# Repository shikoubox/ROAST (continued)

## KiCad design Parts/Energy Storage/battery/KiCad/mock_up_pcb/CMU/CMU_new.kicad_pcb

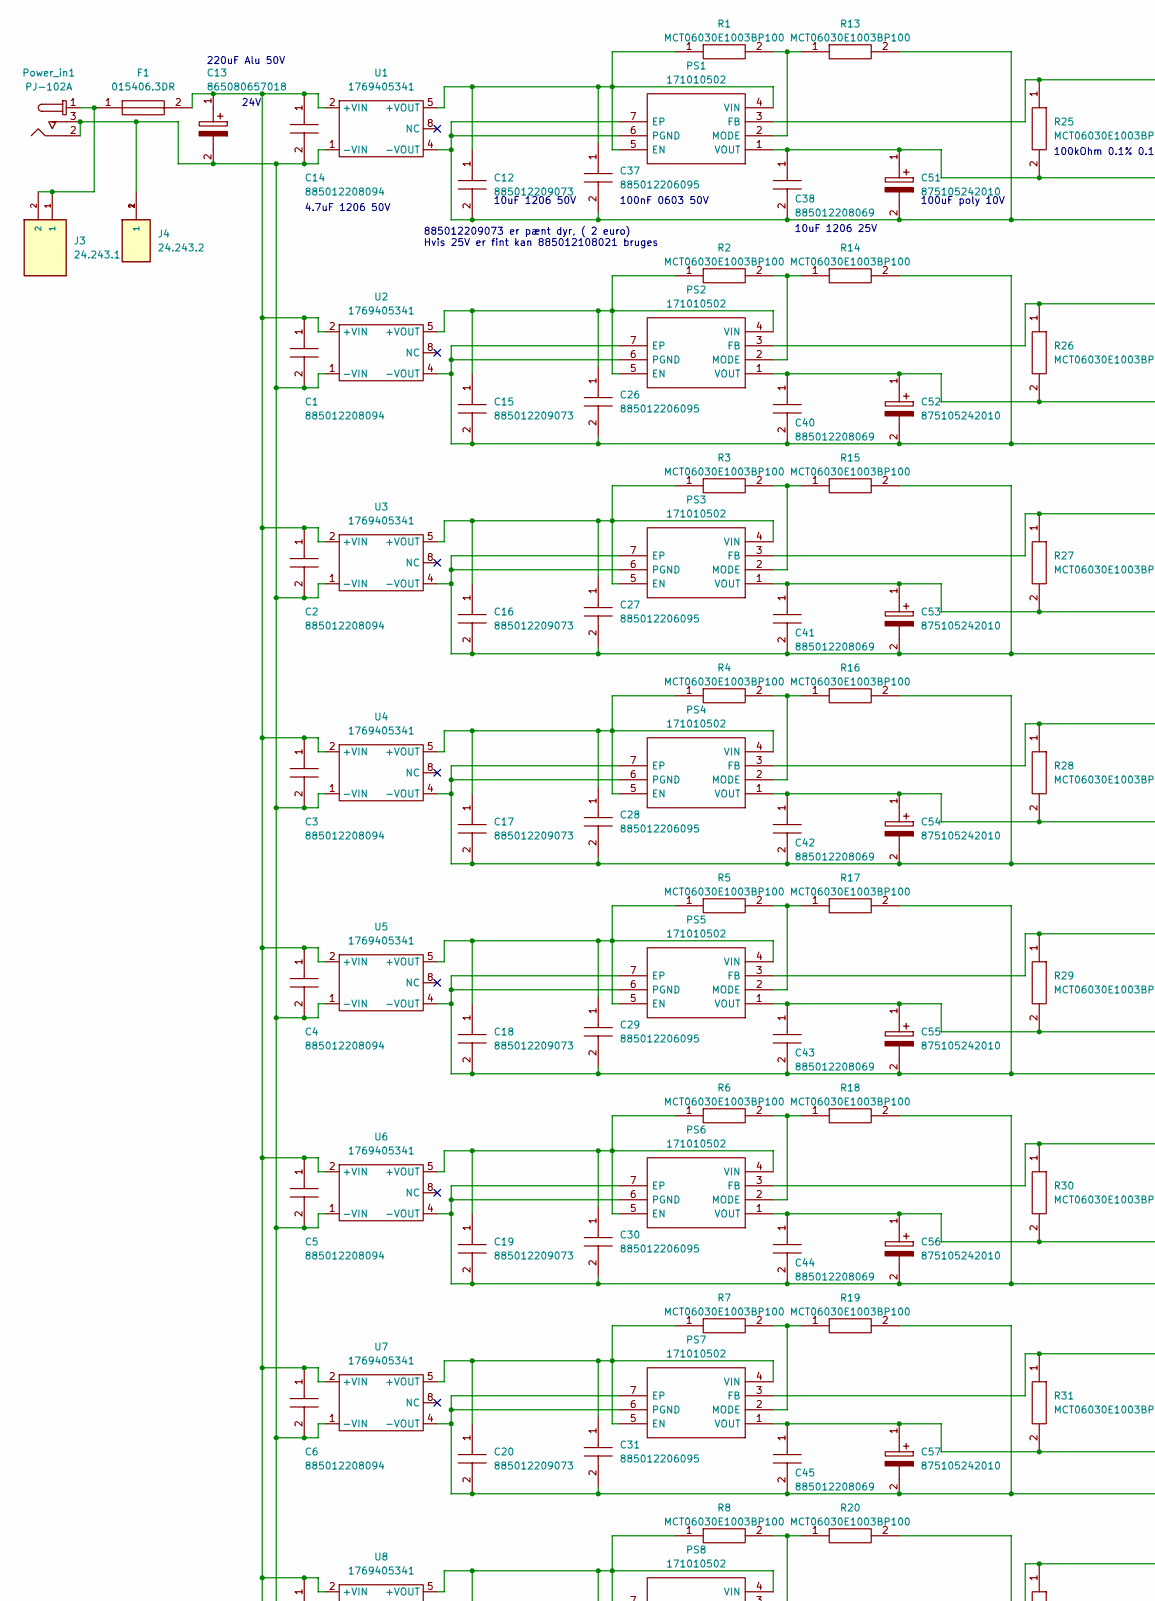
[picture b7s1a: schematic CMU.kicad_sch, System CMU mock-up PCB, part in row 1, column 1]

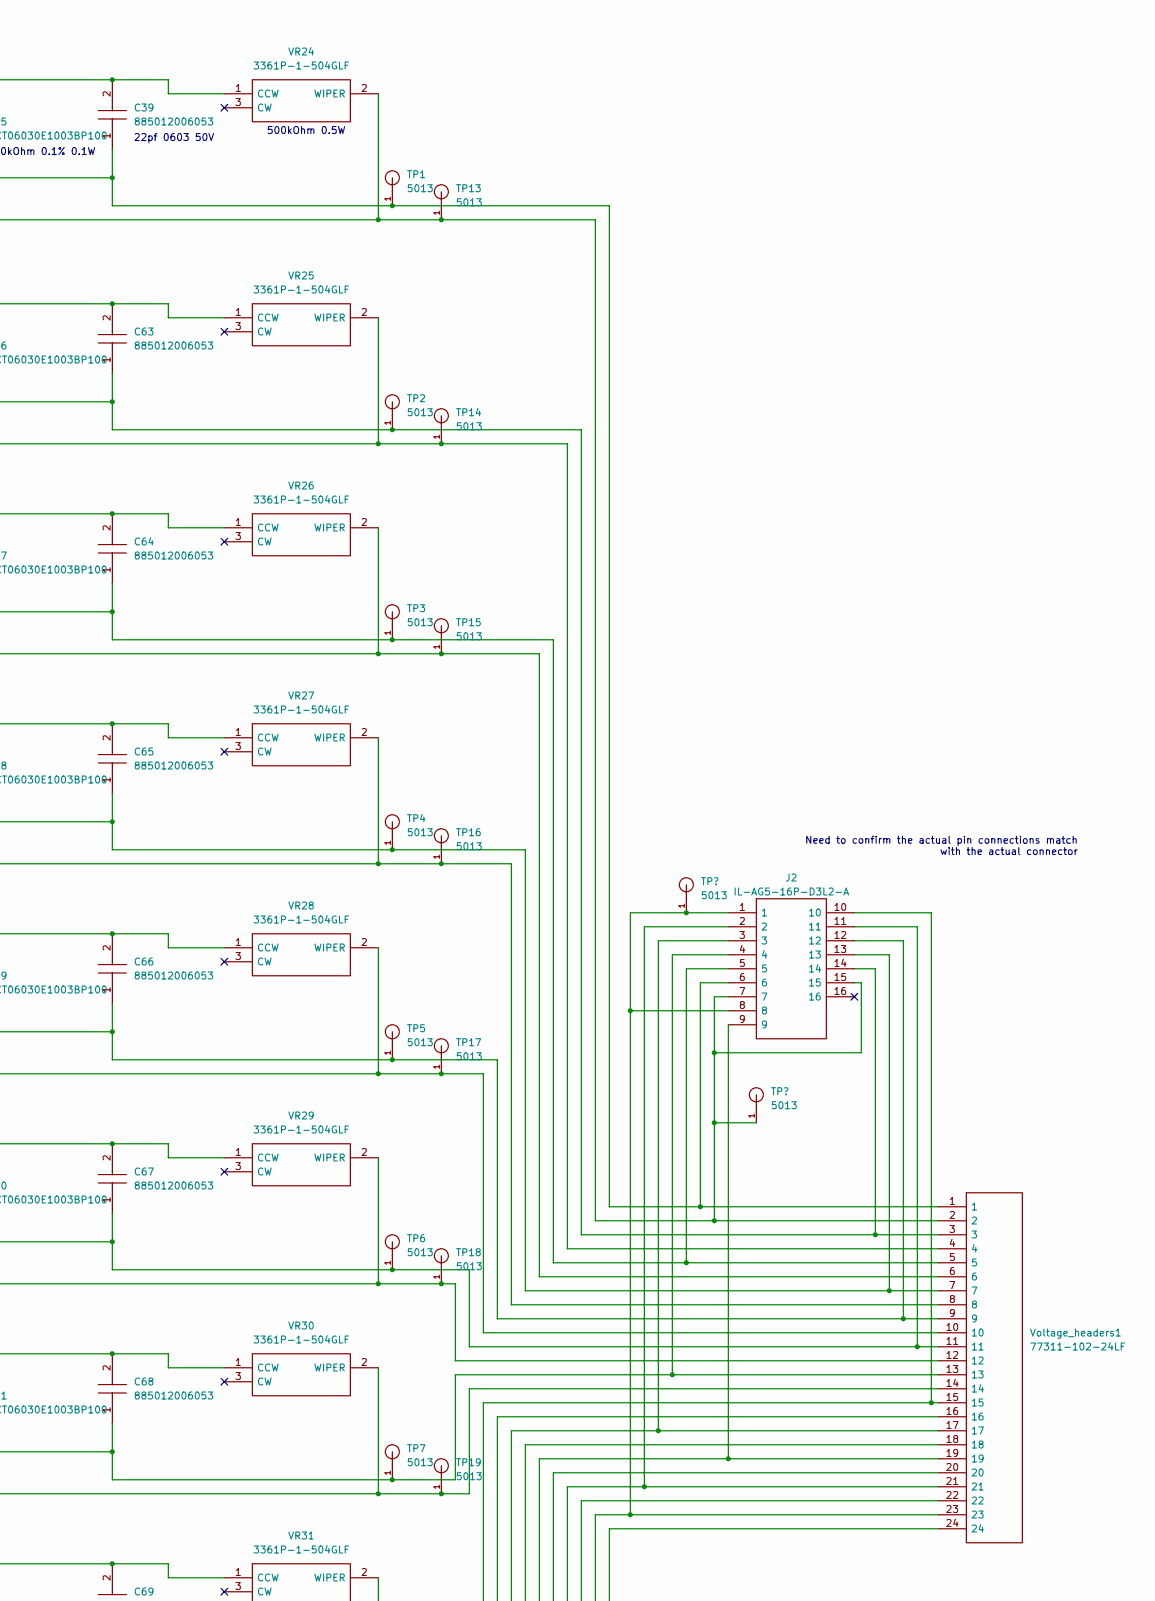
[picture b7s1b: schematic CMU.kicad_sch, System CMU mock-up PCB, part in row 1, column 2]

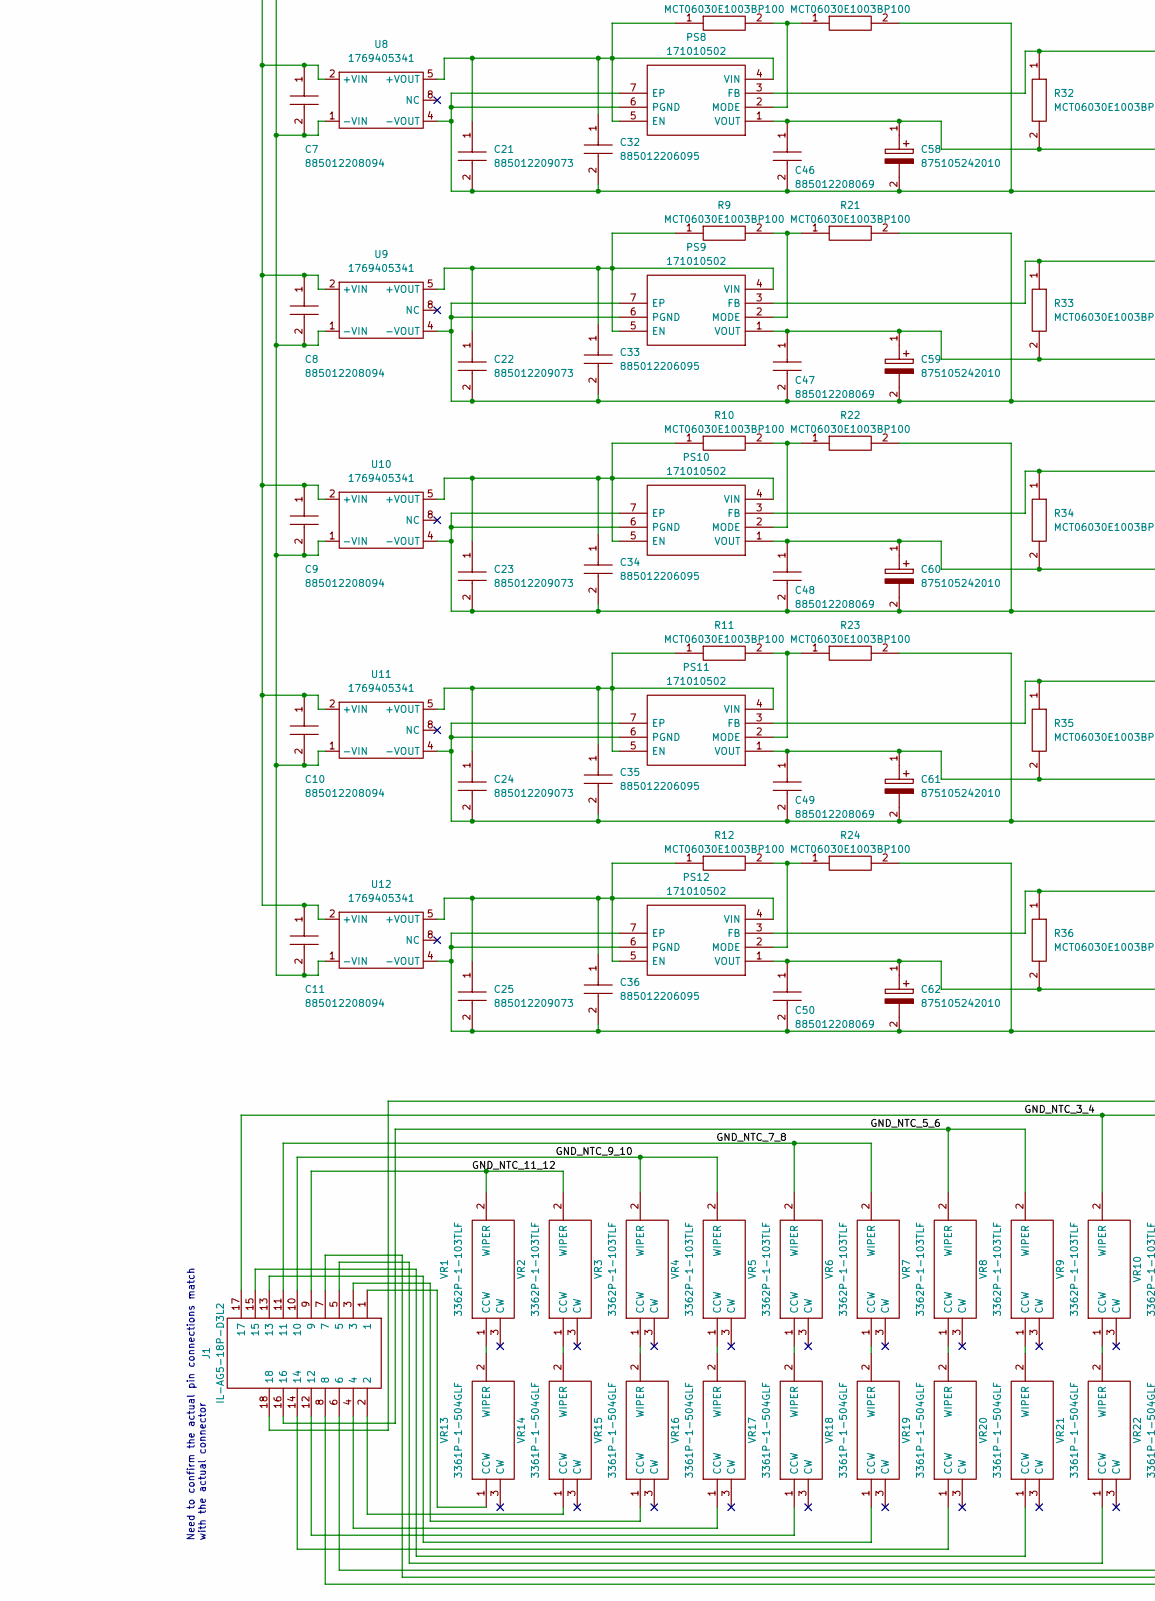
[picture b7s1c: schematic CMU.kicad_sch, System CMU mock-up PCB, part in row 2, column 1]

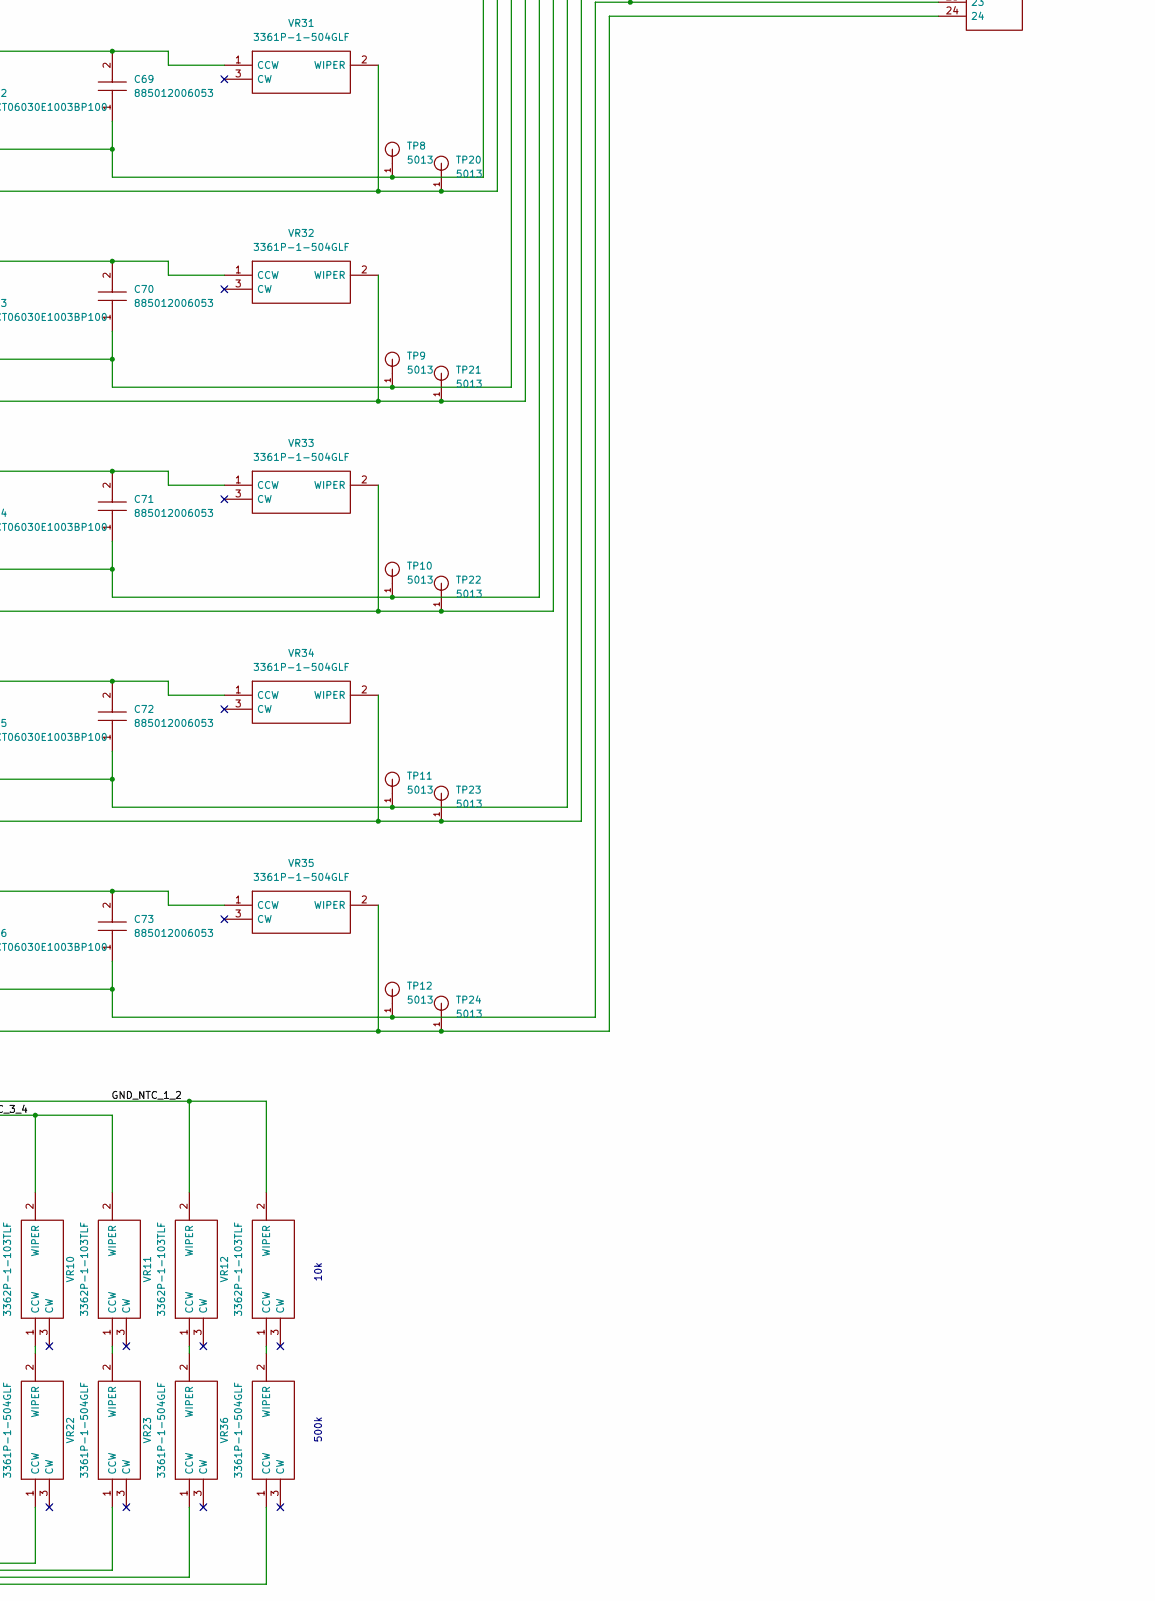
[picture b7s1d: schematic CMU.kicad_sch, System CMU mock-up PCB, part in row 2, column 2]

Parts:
C1, C2, C3, C4, C5, C6, C7, C8, C9, C10, C11, C14: 885012208094; CAPC3216X180N; Mouser Part Number 710-885012208094
C12, C15, C16, C17, C18, C19, C20, C21, C22, C23, C24, C25: 885012209073; CAPC3225X280N; Mouser Part Number 710-885012209073
C13: 865080657018; CAPAE1030X1050N; Mouser Part Number 710-865080657018
C26, C27, C28, C29, C30, C31, C32, C33, C34, C35, C36, C37: 885012206095; CAPC1608X87N; Mouser Part Number 710-885012206095
C38, C40, C41, C42, C43, C44, C45, C46, C47, C48, C49, C50: 885012208069; CAPC3216X180N; Mouser Part Number 710-885012208069
C39, C63, C64, C65, C66, C67, C68, C69, C70, C71, C72, C73: 885012006053; CAPC1608X87N; Mouser Part Number 710-885012006053
C51, C52, C53, C54, C55, C56, C57, C58, C59, C60, C61, C62: 875105242010; CAPAE530X550N; Mouser Part Number 710-875105242010
F1: 015406.3DR; 0154063DR; Mouser Part Number 576-015406.3DR
J1: IL-AG5-18P-D3L2; ILAG518PD3L2; Mouser Part Number 656-IL-AG5-18P-D3L2
J2: IL-AG5-16P-D3L2-A; ILAG516PD3L2A; Mouser Part Number 656-ILAG516PD3L2A
J3: 24.243.1; 242431; Manufacturer_Part_Number 24.243.1
J4: 24.243.2; MULTICOMP_24.243.2; PARTREV 1.0
PS1, PS2, PS3, PS4, PS5, PS6, PS7, PS8, PS9, PS10, PS11, PS12: 171010502; Mouser Part Number 710-171010502
Power_in1: PJ-102A; Barrel_Jack_5.5mmODx2.1mmID_PJ-102A; MPN PJ-102A; Digi-Key_PN CP-102A-ND
R1, R2, R3, R4, R5, R6, R7, R8, R9, R10, R11, R12, R13, R14, R15, R16, R17, R18, R19, R20, R21, R22, R23, R24, R25, R26, R27, R28, R29, R30, R31, R32, R33, R34, R35, R36: MCT06030E1003BP100; RESC1608X55N; Mouser Part Number 594-MCT06030E1003BP1
TP1, TP2, TP3, TP4, TP5, TP6, TP7, TP8, TP9, TP10, TP11, TP12, TP13, TP14, TP15, TP16, TP17, TP18, TP19, TP20, TP21, TP22, TP23, TP24: 5013; TESTPOINT_5013; PARTREV F
U1, U2, U3, U4, U5, U6, U7, U8, U9, U10, U11, U12: 1769405341
VR1, VR2, VR3, VR4, VR5, VR6, VR7, VR8, VR9, VR10, VR11, VR12: 3362P-1-103TLF; 3296P-1-103; Mouser Part Number 652-3362P-1-103TLF
VR13, VR14, VR15, VR16, VR17, VR18, VR19, VR20, VR21, VR22, VR23, VR24, VR25, VR26, VR27, VR28, VR29, VR30, VR31, VR32, VR33, VR34, VR35, VR36: 3361P-1-504GLF; 3361P1253GLF; Mouser Part Number 652-3361P-1-504GLF
Voltage_headers1: 77311-102-24LF; HDRV24W62P0X254_1X24_6096X240X858P; Mouser Part Number 649-77311-102-24LF

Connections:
/GND_NTC_1_2: J1.18, VR11.2 (WIPER), VR12.2 (WIPER)
/GND_NTC_3_4: J1.17, VR9.2 (WIPER), VR10.2 (WIPER)
/GND_NTC_5_6: J1.16, VR7.2 (WIPER), VR8.2 (WIPER)
/GND_NTC_7_8: J1.11, VR5.2 (WIPER), VR6.2 (WIPER)
/GND_NTC_9_10: J1.10, VR3.2 (WIPER), VR4.2 (WIPER)
/GND_NTC_11_12: J1.9, VR1.2 (WIPER), VR2.2 (WIPER)
unnamed: C1.1, C2.1, C3.1, C4.1, C5.1, C6.1, C7.1, C8.1, C9.1, C10.1, C11.1, C13.1, C14.1, F1.2, U1.2 (+VIN), U2.2 (+VIN), U3.2 (+VIN), U4.2 (+VIN), U5.2 (+VIN), U6.2 (+VIN), U7.2 (+VIN), U8.2 (+VIN), U9.2 (+VIN), U10.2 (+VIN), U11.2 (+VIN), U12.2 (+VIN)
unnamed: C1.2, C2.2, C3.2, C4.2, C5.2, C6.2, C7.2, C8.2, C9.2, C10.2, C11.2, C13.2, C14.2, J4.1, J4.2 (1), Power_in1.2, Power_in1.3, U1.1 (-VIN), U2.1 (-VIN), U3.1 (-VIN), U4.1 (-VIN), U5.1 (-VIN), U6.1 (-VIN), U7.1 (-VIN), U8.1 (-VIN), U9.1 (-VIN), U10.1 (-VIN), U11.1 (-VIN), U12.1 (-VIN)
unnamed: C12.1, C37.1, PS1.4 (VIN), PS1.5 (EN), R1.1, U1.5 (+VOUT)
unnamed: C12.2, C37.2, C38.2, C51.2, J2.7, J2.15, PS1.6 (PGND), PS1.7 (EP), R13.2, TP13.1, U1.4 (-VOUT), VR24.2 (WIPER), Voltage_headers1.2
unnamed: C15.1, C26.1, PS2.4 (VIN), PS2.5 (EN), R2.1, U2.5 (+VOUT)
unnamed: C15.2, C26.2, C40.2, C52.2, PS2.6 (PGND), PS2.7 (EP), R14.2, TP14.1, U2.4 (-VOUT), VR25.2 (WIPER), Voltage_headers1.4
unnamed: C16.1, C27.1, PS3.4 (VIN), PS3.5 (EN), R3.1, U3.5 (+VOUT)
unnamed: C16.2, C27.2, C41.2, C53.2, PS3.6 (PGND), PS3.7 (EP), R15.2, TP15.1, U3.4 (-VOUT), VR26.2 (WIPER), Voltage_headers1.6
unnamed: C17.1, C28.1, PS4.4 (VIN), PS4.5 (EN), R4.1, U4.5 (+VOUT)
unnamed: C17.2, C28.2, C42.2, C54.2, PS4.6 (PGND), PS4.7 (EP), R16.2, TP16.1, U4.4 (-VOUT), VR27.2 (WIPER), Voltage_headers1.8
unnamed: C18.1, C29.1, PS5.4 (VIN), PS5.5 (EN), R5.1, U5.5 (+VOUT)
unnamed: C18.2, C29.2, C43.2, C55.2, PS5.6 (PGND), PS5.7 (EP), R17.2, TP17.1, U5.4 (-VOUT), VR28.2 (WIPER), Voltage_headers1.10
unnamed: C19.1, C30.1, PS6.4 (VIN), PS6.5 (EN), R6.1, U6.5 (+VOUT)
unnamed: C19.2, C30.2, C44.2, C56.2, PS6.6 (PGND), PS6.7 (EP), R18.2, TP18.1, U6.4 (-VOUT), VR29.2 (WIPER), Voltage_headers1.12
unnamed: C20.1, C31.1, PS7.4 (VIN), PS7.5 (EN), R7.1, U7.5 (+VOUT)
unnamed: C20.2, C31.2, C45.2, C57.2, PS7.6 (PGND), PS7.7 (EP), R19.2, TP19.1, U7.4 (-VOUT), VR30.2 (WIPER), Voltage_headers1.14
unnamed: C21.1, C32.1, PS8.4 (VIN), PS8.5 (EN), R8.1, U8.5 (+VOUT)
unnamed: C21.2, C32.2, C46.2, C58.2, PS8.6 (PGND), PS8.7 (EP), R20.2, TP20.1, U8.4 (-VOUT), VR31.2 (WIPER), Voltage_headers1.16
unnamed: C22.1, C33.1, PS9.4 (VIN), PS9.5 (EN), R9.1, U9.5 (+VOUT)
unnamed: C22.2, C33.2, C47.2, C59.2, PS9.6 (PGND), PS9.7 (EP), R21.2, TP21.1, U9.4 (-VOUT), VR32.2 (WIPER), Voltage_headers1.18
unnamed: C23.1, C34.1, PS10.4 (VIN), PS10.5 (EN), R10.1, U10.5 (+VOUT)
unnamed: C23.2, C34.2, C48.2, C60.2, PS10.6 (PGND), PS10.7 (EP), R22.2, TP22.1, U10.4 (-VOUT), VR33.2 (WIPER), Voltage_headers1.20
unnamed: C24.1, C35.1, PS11.4 (VIN), PS11.5 (EN), R11.1, U11.5 (+VOUT)
unnamed: C24.2, C35.2, C49.2, C61.2, PS11.6 (PGND), PS11.7 (EP), R23.2, TP23.1, U11.4 (-VOUT), VR34.2 (WIPER), Voltage_headers1.22
unnamed: C25.1, C36.1, PS12.4 (VIN), PS12.5 (EN), R12.1, U12.5 (+VOUT)
unnamed: C25.2, C36.2, C50.2, C62.2, PS12.6 (PGND), PS12.7 (EP), R24.2, TP24.1, U12.4 (-VOUT), VR35.2 (WIPER), Voltage_headers1.24
unnamed: C38.1, C39.1, C51.1, J2.6, PS1.1 (VOUT), R25.2, TP1.1, Voltage_headers1.1
unnamed: C39.2, PS1.3 (FB), R25.1, VR24.1 (CCW)
unnamed: C40.1, C52.1, C63.1, J2.14, PS2.1 (VOUT), R26.2, TP2.1, Voltage_headers1.3
unnamed: C41.1, C53.1, C64.1, J2.5, PS3.1 (VOUT), R27.2, TP3.1, Voltage_headers1.5
unnamed: C42.1, C54.1, C65.1, J2.13, PS4.1 (VOUT), R28.2, TP4.1, Voltage_headers1.7
unnamed: C43.1, C55.1, C66.1, J2.12, PS5.1 (VOUT), R29.2, TP5.1, Voltage_headers1.9
unnamed: C44.1, C56.1, C67.1, J2.11, PS6.1 (VOUT), R30.2, TP6.1, Voltage_headers1.11
unnamed: C45.1, C57.1, C68.1, J2.4, PS7.1 (VOUT), R31.2, TP7.1, Voltage_headers1.13
unnamed: C46.1, C58.1, C69.1, J2.10, PS8.1 (VOUT), R32.2, TP8.1, Voltage_headers1.15
unnamed: C47.1, C59.1, C70.1, J2.3, PS9.1 (VOUT), R33.2, TP9.1, Voltage_headers1.17
unnamed: C48.1, C60.1, C71.1, J2.9, PS10.1 (VOUT), R34.2, TP10.1, Voltage_headers1.19
unnamed: C49.1, C61.1, C72.1, J2.2, PS11.1 (VOUT), R35.2, TP11.1, Voltage_headers1.21
unnamed: C50.1, C62.1, C73.1, J2.1, J2.8, PS12.1 (VOUT), R36.2, TP12.1, Voltage_headers1.23
unnamed: C63.2, PS2.3 (FB), R26.1, VR25.1 (CCW)
unnamed: C64.2, PS3.3 (FB), R27.1, VR26.1 (CCW)
unnamed: C65.2, PS4.3 (FB), R28.1, VR27.1 (CCW)
unnamed: C66.2, PS5.3 (FB), R29.1, VR28.1 (CCW)
unnamed: C67.2, PS6.3 (FB), R30.1, VR29.1 (CCW)
unnamed: C68.2, PS7.3 (FB), R31.1, VR30.1 (CCW)
unnamed: C69.2, PS8.3 (FB), R32.1, VR31.1 (CCW)
unnamed: C70.2, PS9.3 (FB), R33.1, VR32.1 (CCW)
unnamed: C71.2, PS10.3 (FB), R34.1, VR33.1 (CCW)
unnamed: C72.2, PS11.3 (FB), R35.1, VR34.1 (CCW)
unnamed: C73.2, PS12.3 (FB), R36.1, VR35.1 (CCW)
unnamed: F1.1, J3.1, J3.2, Power_in1.1
unnamed: J1.1, VR13.1 (CCW)
unnamed: J1.2, VR14.1 (CCW)
unnamed: J1.3, VR15.1 (CCW)
unnamed: J1.4, VR16.1 (CCW)
unnamed: J1.5, VR21.1 (CCW)
unnamed: J1.6, VR22.1 (CCW)
unnamed: J1.7, VR23.1 (CCW)
unnamed: J1.8, VR36.1 (CCW)
unnamed: J1.12, VR17.1 (CCW)
unnamed: J1.13, VR18.1 (CCW)
unnamed: J1.14, VR19.1 (CCW)
unnamed: J1.15, VR20.1 (CCW)
unnamed: PS1.2 (MODE), R1.2, R13.1
unnamed: PS2.2 (MODE), R2.2, R14.1
unnamed: PS3.2 (MODE), R3.2, R15.1
unnamed: PS4.2 (MODE), R4.2, R16.1
unnamed: PS5.2 (MODE), R5.2, R17.1
unnamed: PS6.2 (MODE), R6.2, R18.1
unnamed: PS7.2 (MODE), R7.2, R19.1
unnamed: PS8.2 (MODE), R8.2, R20.1
unnamed: PS9.2 (MODE), R9.2, R21.1
unnamed: PS10.2 (MODE), R10.2, R22.1
unnamed: PS11.2 (MODE), R11.2, R23.1
unnamed: PS12.2 (MODE), R12.2, R24.1
unnamed: VR1.1 (CCW), VR13.2 (WIPER)
unnamed: VR10.1 (CCW), VR22.2 (WIPER)
unnamed: VR11.1 (CCW), VR23.2 (WIPER)
unnamed: VR12.1 (CCW), VR36.2 (WIPER)
unnamed: VR2.1 (CCW), VR14.2 (WIPER)
unnamed: VR3.1 (CCW), VR15.2 (WIPER)
unnamed: VR4.1 (CCW), VR16.2 (WIPER)
unnamed: VR5.1 (CCW), VR17.2 (WIPER)
unnamed: VR6.1 (CCW), VR18.2 (WIPER)
unnamed: VR7.1 (CCW), VR19.2 (WIPER)
unnamed: VR8.1 (CCW), VR20.2 (WIPER)
unnamed: VR9.1 (CCW), VR21.2 (WIPER)

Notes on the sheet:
10k
10uF 1206 25V
100nF 0603 50V
220uF Alu 50V
4.7uF 1206 50V
24V
Need to confirm the actual pin connections match with the actual connector
500kOhm 0.5W
100kOhm 0.1% 0.1W
500k
100uF poly 10V
885012209073 er pænt dyr, ( 2 euro) Hvis 25V er fint kan 885012108021 bruges
22pf 0603 50V
10uF 1206 50V

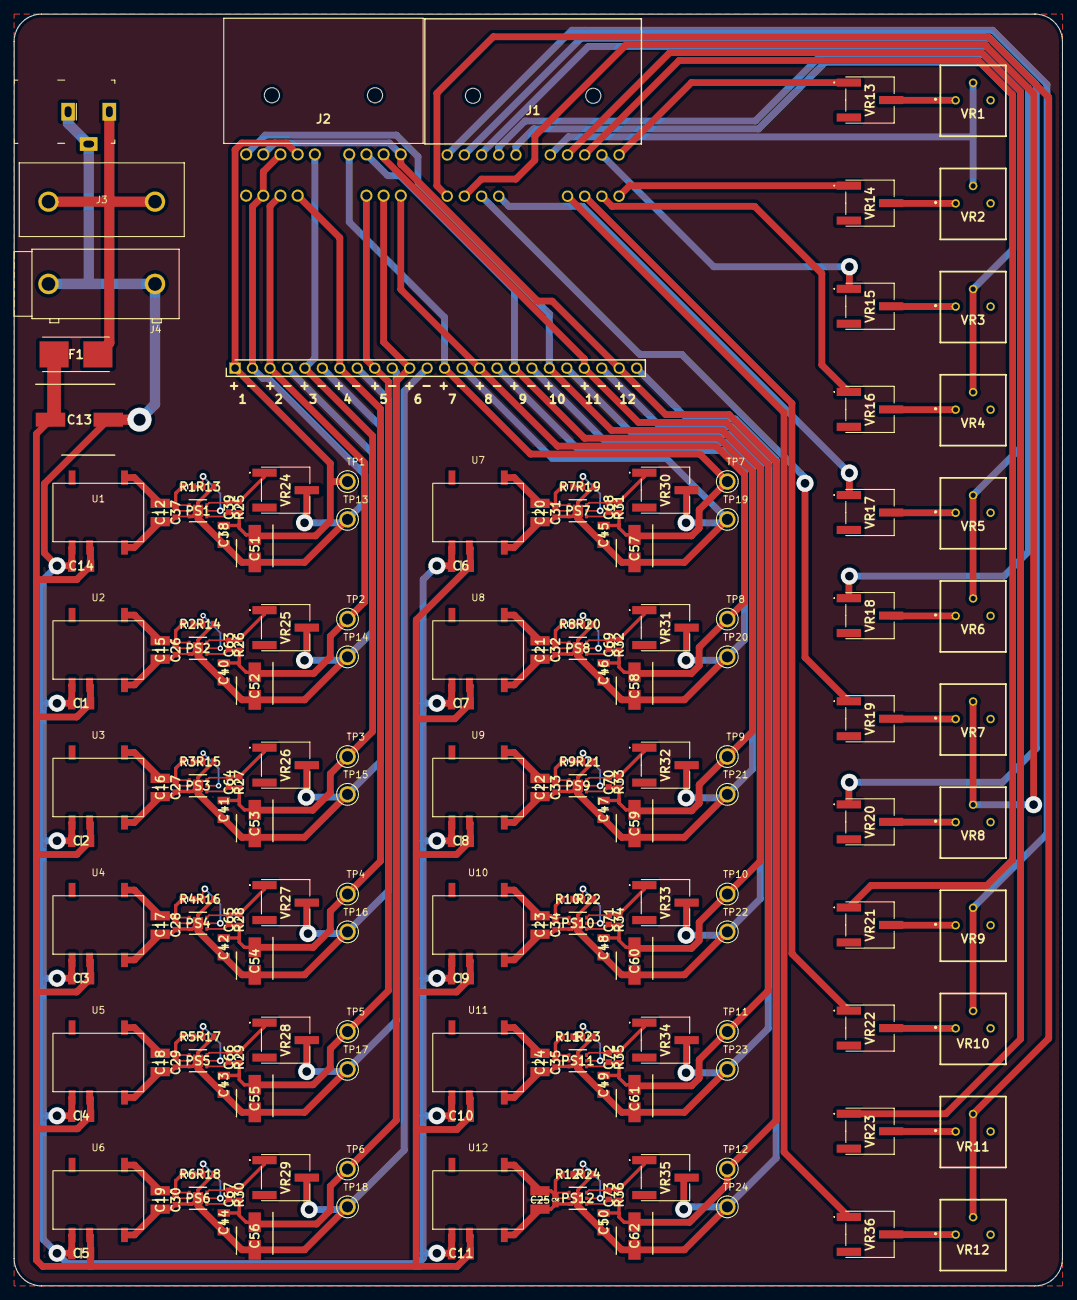
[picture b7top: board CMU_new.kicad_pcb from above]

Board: 2 copper layers, 152.5 x 185.0 mm, 200 parts (0 on the bottom side), 93 nets.

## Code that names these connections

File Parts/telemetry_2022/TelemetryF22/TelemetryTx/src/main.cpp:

// Tx Code
#include <Arduino.h>
#include <SPI.h>
#include <SDFat.h>
#include <RF24.h>
#include <eXoCAN.h>
#include <STM32RTC.h>
#define nRF24_IQR PA8
#define PIPE 0xE8E8F0F0E1LL
#define CE_PIN PB10
#define CSN_PIN PA9
#define CS_PIN PA4
#define BLK_L 512          // Block size (Bytes)
#define BLK_BUF_L 1        // Number of blocks in block buffer
#define PKG_L 32           // Pacakge size (Bytes)
#define PKG_BUF_L 1        // Number of packages in package buffer
#define MSG_L 8            // CAN message length (Bytes)
#define ID_L 2             // CAN id length (Bytes)
#define FRM_L MSG_L + ID_L // Frame length (Bytes)
#define TIME_L 2           // Time stamp length (Bytes)
#define BAUD 9600

/* RTC declarations */
STM32RTC &rtc = STM32RTC::getInstance(); // Get the rtc object
uint8_t seconds;
uint8_t minutes;
uint8_t hours;

/* SD declarations */
SdFat sd;
SdFile myFile;

/* RF declarations */
RF24 radio(CE_PIN, CSN_PIN); // Radio object (CE,CSN)

/* CAN declarations */
eXoCAN can(STD_ID_LEN, BR500K, PORTB_8_9_WIRE_PULLUP);

/*Buffer declarations */
uint8_t block[BLK_BUF_L][BLK_L];
uint8_t package[PKG_BUF_L][PKG_L]; // RF payload data
uint32_t idx = 0;
uint32_t pkgIdx = 0;
uint32_t blkIdx = 0;

void nRF24_ISR();
bool radioWritePayload(uint8_t *data, uint8_t data_len);
void rtcTimeToInt(const char *str);
void sdWrite();
void canISR();

void setup()
{
  /* RTC config */
  rtc.setClockSource(STM32RTC::LSE_CLOCK);
  rtc.begin(0);
  rtcTimeToInt(__TIME__);
  if (
      (rtc.getHours() < hours) ||
      (rtc.getHours() == hours && rtc.getMinutes() < minutes) ||
      (rtc.getHours() == hours && rtc.getMinutes() == minutes && rtc.getSeconds() < seconds))
  {
    rtc.setTime(hours, minutes, seconds);
  }

  /* Serial config */

  /* LED config */
  pinMode(LED_BUILTIN, OUTPUT);

  /* SD config */
  sd.begin(CS_PIN, 18e6); // SPI speed = 18MHz
  myFile.open("datalog.txt", FILE_WRITE);

  /* Radio config */
  SPI.begin();
  radio.begin();
  radio.setAddressWidth(3);
  radio.setCRCLength(RF24_CRC_8);
  radio.setDataRate(RF24_2MBPS); // Options: RF24_1MBPS, RF24_2MBPS, RF24_250KBPS
  radio.setPALevel(RF24_PA_LOW, 0);
  radio.openWritingPipe(PIPE);
  radio.stopListening();
  radioWritePayload(package[pkgIdx], PKG_L); // Fill Tx buffer
  radioWritePayload(package[pkgIdx], PKG_L); // Fill Tx buffer
  radioWritePayload(package[pkgIdx], PKG_L); // Fill Tx buffer

  /* Interrupt config */
  radio.maskIRQ(0, 0, 1);
  pinMode(nRF24_IQR, INPUT);
  attachInterrupt(digitalPinToInterrupt(nRF24_IQR), nRF24_ISR, FALLING);
  can.attachInterrupt(canISR);
}

void loop()
{
  if (!(millis() % 8)){ // write to sd card every 8ms
    sdWrite();
  }
}

void canISR() // get CAN bus frame passed by a filter into fifo0
{
  digitalWrite(LED_BUILTIN, LOW);
  int id;
  int fltIdx;
  uint8_t msg[MSG_L];
  can.receive(id, fltIdx, msg); // Empties CAN FIFO
  uint8_t i;
  for (i = 0; i < ID_L; i++){ // Write id to package
    package[pkgIdx][idx] = (id >> (8 * (ID_L - i - 1))) & 0x00FF;
    idx++;
  }
  for (i = ID_L; i < FRM_L; i++){ // Write msg to package
    package[pkgIdx][idx] = msg[i - ID_L];
    idx++;
  }
  if (idx >= 3 * FRM_L){ // A package contains 3 frames.
    idx = 0;
    pkgIdx++;
  }
  if (pkgIdx >= PKG_BUF_L){
    pkgIdx = 0;
  }
  digitalWrite(LED_BUILTIN, HIGH);
}

void nRF24_ISR() // This runs when nRF24 module interupts the MCU
{
  package[pkgIdx][PKG_L - 1] = rtc.getSeconds();
  package[pkgIdx][PKG_L - 2] = rtc.getMinutes();
  if (radioWritePayload(package[pkgIdx], PKG_L)){ // Upload data via SPI
    // digitalWrite(LED_BUILTIN,HIGH);
  }
  else{
    // digitalWrite(LED_BUILTIN,LOW);
  }
}

bool radioWritePayload(uint8_t *data, uint8_t data_len)
{
  digitalWrite(CE_PIN, HIGH);
  SPI.beginTransaction(CSN_PIN, SPISettings(RF24_SPI_SPEED, MSBFIRST, SPI_MODE0));
  uint8_t status = SPI.transfer(CSN_PIN, 0x27, SPI_CONTINUE); // 0x27 is a write register command. Returns status register.
  SPI.transfer(CSN_PIN, 0x77, SPI_LAST);                      // 0x77 resets satus register (rst exti).
  SPI.transfer(CSN_PIN, 0xA0, SPI_CONTINUE);                  // 0xA0 is a wirte Tx buffer command.
  SPI.transfer(CSN_PIN, data, data_len, SPI_LAST);            // writing data over SPI
  SPI.endTransaction(CSN_PIN);
  digitalWrite(CE_PIN, LOW);
  return (bool)(status >> (5)) & 1; // 5th bit in status reg tells us if data transfered succesfully
}

void sdWrite()
{
  detachInterrupt(digitalPinToInterrupt(nRF24_IQR));
  myFile.write(block[0], BLK_L); // Log data to sd
  if (!(millis() % 3000)){ // Save sd card file every 3s
    myFile.close();
    myFile.open("datalog.txt", FILE_WRITE);
  }
  radioWritePayload(package[pkgIdx], PKG_L); // Resume RF transmission.
  attachInterrupt(digitalPinToInterrupt(nRF24_IQR), nRF24_ISR, FALLING);
}

void rtcTimeToInt(const char *str)
{
  seconds = 0;
  minutes = 0;
  hours = 0;
  int32_t hms = 0, multiplier = 1, strIdx;
  for (strIdx = 0; str[strIdx]; strIdx++){}
  strIdx--;
  for (; strIdx >= 0; strIdx--){
    if (str[strIdx] == ':'){
      hms++;
      multiplier = 1;
    }
    else if (str[strIdx] >= '0' && str[strIdx] <= '9'){
      if (hms == 0){
        seconds += (str[strIdx] - '0') * multiplier;
      }
      if (hms == 1){
        minutes += (str[strIdx] - '0') * multiplier;
      }
      if (hms == 2){
        hours += (str[strIdx] - '0') * multiplier;
      }
      multiplier *= 10;
    }
  }
}

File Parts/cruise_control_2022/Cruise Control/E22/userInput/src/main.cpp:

#include <SPI.h>
#include <mcp_can.h>
#include <Arduino.h>
#include <stdlib.h>
#include <stdio.h>
#include <stdint.h>
#include <string.h>
#include <inttypes.h>

// Define IO-pins names
#define speederAnalogeIn_PIN A0
#define speederPWMIn_PIN PA11
#define cruiseControlPlus_PIN PA8
#define cruiseControlMinus_PIN PB10
#define breakOnIn_PIN PC7
#define cruiseControlOnIn_PIN PA9
#define cruiseControlOnLED_PIN PB8
#define breakeOnLED_PIN PB9


// Choose the SPI pin and pass it to the CAN libary
const int spiCSPin = 10;
MCP_CAN CAN(spiCSPin);

void setup(){
  // Begin serial communication
  Serial.println("Setup 1");
  Serial.begin(115200);

  //Tjek the CAN bus is ready
  while (CAN_OK != CAN.begin(CAN_500KBPS)){
    Serial.println("CAN BUS init Failed");
    delay(100);
  }
  Serial.println("CAN BUS Shield Init OK!");


  // Set up IO-pins
  pinMode(speederAnalogeIn_PIN,INPUT);
  pinMode(cruiseControlOnLED_PIN, OUTPUT); 
  pinMode(breakeOnLED_PIN, OUTPUT); 
  pinMode(breakOnIn_PIN,INPUT);
  pinMode(cruiseControlOnIn_PIN,INPUT);
  pinMode(cruiseControlPlus_PIN,INPUT);
  pinMode(cruiseControlMinus_PIN,INPUT);
  pinMode(speederPWMIn_PIN,INPUT);
}

// Funtions to detect edges on the speeder PWM signal
void rising() ;
void falling() ;

// Funtions to send values over CAN:
void set16BitIntOnCAN(unsigned char a[], uint16_t n);
void setCruiseControlBreakPlusMinus(unsigned char a[], unsigned char cc_on, unsigned char b_on,unsigned char plus_on, unsigned char minus_on);

// Values used for the PWM input
volatile int pwm_value = 0;
volatile int prev_time = 0;
int pwm_mapped;

// Array that stores data before it is send
unsigned char stmp[8] = {0, 0, 0, 0, 0, 0, 0, 0};

// Sets the id for CAN messeges send by this MCU
int id = 41;

// Sets the defalt length for CAN messeges send by this MCU
unsigned char l = 3;

// len and buf will be filed with data form the CAN bus
unsigned char len = 0;
unsigned char buf[8] = {0,0,0,0,0,0,0,0};


// Values for input dectection
// Gets the curent input from the buttons 
unsigned char cc_in = 0;
unsigned char b_in = 0;
unsigned char plus_in = 0;
unsigned char minus_in = 0;

// Stores the last input and is used for rising edge detection
unsigned char cc_s= 0;
unsigned char b_s = 0;
unsigned char plus_s = 0;
unsigned char minus_s = 0;

// Logic values for cruise control and breake state
bool cc_on = false;
bool b_on = false;
bool plus_on = false;
bool minus_on = false;

// Used to save the time the last messege was send
unsigned long timeOfLastMessege = 0; 

// Time between CAN messages in ms
uint16_t msBetweenCANMessages = 50;

int analogSpeederIn = analogRead(speederAnalogeIn_PIN);


int v = 0;
uint16_t rpm = 0;
uint8_t analogThrottel = 0;
uint8_t PWMThrottel = 0;
float throttelOut = 0;
uint16_t throttelSend = 0;

void loop()
{ 
  analogSpeederIn = analogRead(speederAnalogeIn_PIN);
  analogThrottel = map(analogSpeederIn, 0, 1023, 0, 100); 
  PWMThrottel = pwm_mapped;

  b_s = b_in;
  b_in = digitalRead(breakOnIn_PIN);
  plus_in = digitalRead(cruiseControlPlus_PIN);
  minus_in = digitalRead(cruiseControlMinus_PIN);
  cc_in = digitalRead(cruiseControlOnIn_PIN);

  if(b_s && !b_in){
    b_on = false;
    //v = analogThrottel; 
    throttelOut = 0;
  }
 

  if(!b_in){
    digitalWrite(breakeOnLED_PIN, b_in);

    if(cc_in && !cc_s){
      if(!cc_on){
        cc_on = true;
        digitalWrite(cruiseControlOnLED_PIN, cc_on);
      }else{
        cc_on = false;
        digitalWrite(cruiseControlOnLED_PIN, cc_on);
      }
      
    }

    if(cc_in){
      cc_s = 1;
    } else{
      cc_s = 0;
    }
    
    if(cc_on){
      if(plus_in && !plus_s){
        //v += 5;
        plus_on = true;
      }

      if(plus_in){
        plus_s = 1;
      } else{
        plus_s = 0;
      }

      if(minus_in && !minus_s){
        //v -= 5;
        minus_on = true;
      }
  
      if(minus_in){
        minus_s = 1;
      } else{
        minus_s = 0;
      }
    }else{
      //v = analogeThrottel;
      throttelOut = (analogThrottel + PWMThrottel)/2;
    }
    
  } else {
    b_on = true;
    cc_on = false;
    digitalWrite(breakeOnLED_PIN, b_in);
    digitalWrite(cruiseControlOnLED_PIN, cc_on);
    //v = 0;
    throttelOut = 0;
  }

  /*
  if(v < 0){
    v = 0;
  }else if(v > 120){
    v = 120;
  }
  */
  if(throttelOut < 0){
    throttelOut = 0;
  } else if(throttelOut > 100){
    throttelOut = 100;
  }


  if((millis() - timeOfLastMessege) > msBetweenCANMessages){
    timeOfLastMessege = millis();
    //rpm = (uint16_t)(v*12.91490549);
    throttelSend =  (uint16_t) throttelOut;
    set16BitIntOnCAN(stmp,throttelSend);
    setCruiseControlBreakPlusMinus(stmp,cc_on,b_on,plus_on,minus_on);
    plus_on = false;
    minus_on = false;
    
    CAN.sendMsgBuf(id, 0, l, stmp);
  }
  
}

void rising(){
  attachInterrupt(speederPWMIn_PIN, falling, FALLING);
  prev_time = micros();
}
 
void falling(){
  attachInterrupt(speederPWMIn_PIN, rising, RISING);
  pwm_value = micros()-prev_time;

  // Limit values is set to match test done with the speeder, to encure the input to the maped function is not excited. 
  if(pwm_value<381){
    pwm_value = 381;
  } else if(pwm_value>2937){
    pwm_value = 2937;
  }
  pwm_mapped = map(pwm_value, 381, 2937, 0, 100); 
  
}

void set16BitIntOnCAN(unsigned char a[], uint16_t n) {
  a[1] = (n & 0x000000000000FF00U) >> 8;
  a[0] = (n & 0x00000000000000FFU);
}

void setCruiseControlBreakPlusMinus(unsigned char a[], unsigned char cc_on, unsigned char b_on,unsigned char plus_on, unsigned char minus_on){
  a[2] = ((cc_on << 3) & 0x08U) | ((plus_on << 2) & 0x04U) | ((cc_on << 1) & 0x02U) | (b_on & 0x01U);
}

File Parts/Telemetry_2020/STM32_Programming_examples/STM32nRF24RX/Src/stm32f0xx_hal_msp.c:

/* USER CODE BEGIN Header */
/**
  ******************************************************************************
  * File Name          : stm32f0xx_hal_msp.c
  * Description        : This file provides code for the MSP Initialization 
  *                      and de-Initialization codes.
  ******************************************************************************
  * @attention
  *
  * <h2><center>&copy; Copyright (c) 2020 STMicroelectronics.
  * All rights reserved.</center></h2>
  *
  * This software component is licensed by ST under BSD 3-Clause license,
  * the "License"; You may not use this file except in compliance with the
  * License. You may obtain a copy of the License at:
  *                        opensource.org/licenses/BSD-3-Clause
  *
  ******************************************************************************
  */
/* USER CODE END Header */

/* Includes ------------------------------------------------------------------*/
#include "main.h"
/* USER CODE BEGIN Includes */

/* USER CODE END Includes */

/* Private typedef -----------------------------------------------------------*/
/* USER CODE BEGIN TD */

/* USER CODE END TD */

/* Private define ------------------------------------------------------------*/
/* USER CODE BEGIN Define */
 
/* USER CODE END Define */

/* Private macro -------------------------------------------------------------*/
/* USER CODE BEGIN Macro */

/* USER CODE END Macro */

/* Private variables ---------------------------------------------------------*/
/* USER CODE BEGIN PV */

/* USER CODE END PV */

/* Private function prototypes -----------------------------------------------*/
/* USER CODE BEGIN PFP */

/* USER CODE END PFP */

/* External functions --------------------------------------------------------*/
/* USER CODE BEGIN ExternalFunctions */

/* USER CODE END ExternalFunctions */

/* USER CODE BEGIN 0 */

/* USER CODE END 0 */
/**
  * Initializes the Global MSP.
  */
void HAL_MspInit(void)
{
  /* USER CODE BEGIN MspInit 0 */

  /* USER CODE END MspInit 0 */

  __HAL_RCC_SYSCFG_CLK_ENABLE();
  __HAL_RCC_PWR_CLK_ENABLE();

  /* System interrupt init*/

  /* USER CODE BEGIN MspInit 1 */

  /* USER CODE END MspInit 1 */
}

/**
* @brief SPI MSP Initialization
* This function configures the hardware resources used in this example
* @param hspi: SPI handle pointer
* @retval None
*/
void HAL_SPI_MspInit(SPI_HandleTypeDef* hspi)
{
  GPIO_InitTypeDef GPIO_InitStruct = {0};
  if(hspi->Instance==SPI1)
  {
  /* USER CODE BEGIN SPI1_MspInit 0 */

  /* USER CODE END SPI1_MspInit 0 */
    /* Peripheral clock enable */
    __HAL_RCC_SPI1_CLK_ENABLE();
  
    __HAL_RCC_GPIOA_CLK_ENABLE();
    /**SPI1 GPIO Configuration    
    PA5     ------> SPI1_SCK
    PA6     ------> SPI1_MISO
    PA7     ------> SPI1_MOSI 
    */
    GPIO_InitStruct.Pin = GPIO_PIN_5|GPIO_PIN_6|GPIO_PIN_7;
    GPIO_InitStruct.Mode = GPIO_MODE_AF_PP;
    GPIO_InitStruct.Pull = GPIO_NOPULL;
    GPIO_InitStruct.Speed = GPIO_SPEED_FREQ_HIGH;
    GPIO_InitStruct.Alternate = GPIO_AF0_SPI1;
    HAL_GPIO_Init(GPIOA, &GPIO_InitStruct);

  /* USER CODE BEGIN SPI1_MspInit 1 */

  /* USER CODE END SPI1_MspInit 1 */
  }

}

/**
* @brief SPI MSP De-Initialization
* This function freeze the hardware resources used in this example
* @param hspi: SPI handle pointer
* @retval None
*/
void HAL_SPI_MspDeInit(SPI_HandleTypeDef* hspi)
{
  if(hspi->Instance==SPI1)
  {
  /* USER CODE BEGIN SPI1_MspDeInit 0 */

  /* USER CODE END SPI1_MspDeInit 0 */
    /* Peripheral clock disable */
    __HAL_RCC_SPI1_CLK_DISABLE();
  
    /**SPI1 GPIO Configuration    
    PA5     ------> SPI1_SCK
    PA6     ------> SPI1_MISO
    PA7     ------> SPI1_MOSI 
    */
    HAL_GPIO_DeInit(GPIOA, GPIO_PIN_5|GPIO_PIN_6|GPIO_PIN_7);

  /* USER CODE BEGIN SPI1_MspDeInit 1 */

  /* USER CODE END SPI1_MspDeInit 1 */
  }

}

/**
* @brief UART MSP Initialization
* This function configures the hardware resources used in this example
* @param huart: UART handle pointer
* @retval None
*/
void HAL_UART_MspInit(UART_HandleTypeDef* huart)
{
  GPIO_InitTypeDef GPIO_InitStruct = {0};
  if(huart->Instance==USART2)
  {
  /* USER CODE BEGIN USART2_MspInit 0 */

  /* USER CODE END USART2_MspInit 0 */
    /* Peripheral clock enable */
    __HAL_RCC_USART2_CLK_ENABLE();
  
    __HAL_RCC_GPIOA_CLK_ENABLE();
    /**USART2 GPIO Configuration    
    PA2     ------> USART2_TX
    PA15     ------> USART2_RX 
    */
    GPIO_InitStruct.Pin = GPIO_PIN_2|GPIO_PIN_15;
    GPIO_InitStruct.Mode = GPIO_MODE_AF_PP;
    GPIO_InitStruct.Pull = GPIO_NOPULL;
    GPIO_InitStruct.Speed = GPIO_SPEED_FREQ_HIGH;
    GPIO_InitStruct.Alternate = GPIO_AF1_USART2;
    HAL_GPIO_Init(GPIOA, &GPIO_InitStruct);

  /* USER CODE BEGIN USART2_MspInit 1 */

  /* USER CODE END USART2_MspInit 1 */
  }

}

/**
* @brief UART MSP De-Initialization
* This function freeze the hardware resources used in this example
* @param huart: UART handle pointer
* @retval None
*/
void HAL_UART_MspDeInit(UART_HandleTypeDef* huart)
{
  if(huart->Instance==USART2)
  {
  /* USER CODE BEGIN USART2_MspDeInit 0 */

  /* USER CODE END USART2_MspDeInit 0 */
    /* Peripheral clock disable */
    __HAL_RCC_USART2_CLK_DISABLE();
  
    /**USART2 GPIO Configuration    
    PA2     ------> USART2_TX
    PA15     ------> USART2_RX 
    */
    HAL_GPIO_DeInit(GPIOA, GPIO_PIN_2|GPIO_PIN_15);

  /* USER CODE BEGIN USART2_MspDeInit 1 */

  /* USER CODE END USART2_MspDeInit 1 */
  }

}

/* USER CODE BEGIN 1 */

/* USER CODE END 1 */

/************************ (C) COPYRIGHT STMicroelectronics *****END OF FILE****/

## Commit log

2025-01-24 PCB
    A WIP PCB for the rat
2025-01-24 Rename gitignore to .gitignore
2025-01-27 backup
2025-01-28 pcb backup
2025-01-28 Organising parts folder
2025-01-28 Button_code
2025-01-28 Renamed files containing Ø
2025-01-28 Updated last files with uncommon symbols
2025-01-28 Trying to remove nasty files
2025-01-28 pcb progress backup
2025-01-29 PCB v1
2025-01-29 KiCad after review 1
    Spinat skal hjem og gro, Ost tager over og arbejder videre efter hans gode første review.
2025-01-29 KiCad cheatsheet
2025-01-29 Kicad drawing update
2025-01-31 Trying to fix bad naming again.
2025-01-31 slight changes in schematic
2025-01-31 Trying to add the deleted files
2025-01-31 Trying to remove them again
2025-01-31 trying to remove dead files
2025-01-31 Deleted remaining dead files
2025-01-31 Deleted last dead file and renamed telemetry folders, according to their year.
2025-01-31 PCB work update
2025-02-20 All versions
    All versions from prototype 0.1 to final V5 with raw files.
2025-02-20 removed unneeded
2025-03-25 Telemetry_2024_pdf
    + Patch antenna project
2025-04-24 Dashboard electron
2025-05-30 Updated the project so it reads values from a .csv file
2025-05-30 css update to be lil bigger text
2025-06-04 Initial commit on orphan branch
2025-06-04 Added dashboard folder
2025-06-05 Readme updates
2025-06-05 paste
2025-06-06 Update to dashboard
2025-06-06 Updated_names + csv
2025-06-06 Pulled dashboard to pi_dashboard
2025-06-06 Included the new data.csv
2025-06-09 Update to dashboard
    add data.py
2025-06-09 Radio setup scripts
2025-06-09 More changes to README
2025-06-09 Revisioned version of RFM script
2025-06-09 Better version of the rfm69hcw .py script
2025-06-09 git notes to README
2025-06-09 RF changes
2025-06-09 Cleanup and try to automatise
2025-06-09 Error correction
2025-06-09 Bug fixes
2025-06-09 Bug fixes?
2025-06-09 adding the commit
2025-06-09 update pin
2025-06-10 Dashboard_update.V2.1
    Data.py + css
2025-06-10 rfm69 update
2025-06-10 Fix readme and more changes to RFM module
2025-06-10 More changes and tweaks to RFM code
2025-06-10 rfm69hcw small change
2025-06-10 Better version of the rfm69hcw.py script
2025-06-10 updating rfm69hcw for test on pi
2025-06-10 Test new setup
2025-06-10 main.js go faster
2025-06-10 Revert "updating rfm69hcw for test on pi"
    This reverts commit 7bb67f8a7294224f21d582e892c468cbdaad0d15.
2025-06-11 deleted unused files, and removed csv handling from _rfm69hcw.py
2025-06-11 update.V0
2025-06-11 pieces of code
2025-06-11 new_code_update_CSV
    Error handeling
2025-06-11 Log and update feature
2025-06-11 update main.js 10/sek
2025-06-11 Moved data manipulation to different script
2025-06-11 Decoding capability
2025-06-11 fixed data manipulation error
2025-06-11 Trying to move curses into curses file
2025-06-11 Fixing curses bugs
2025-06-11 Try to fix RF responsibility
2025-06-11 RF bug test
2025-06-11 update to byte handler
2025-06-11 Correct byte handling
2025-06-11 typo
2025-06-12 Send test packet to csv handler
2025-06-12 Send test packet to csv byte handler
2025-06-12 bug fix
2025-06-12 bug fix test
2025-06-12 test
2025-06-12 stable
2025-06-12 test if bug was fixed
2025-06-12 Try with try:
2025-06-12 Fixing blunder
2025-06-12 Renaming files
2025-06-12 Moved files, and updated files
2025-06-12 updated initialisation of rfm69
2025-06-12 Fixing .csv to include bytearrays
2025-06-12 less debugs
2025-06-13 Updated electron app looks
2025-06-13 dBm added to the electron app
2025-06-13 Moved buttons to a more sensical place
2025-06-13 Updated files, without testing them, for rssi capabilities, and cleaner code
2025-06-13 Bug fix attempt
2025-06-13 added .gitignore as well as fixed float int confusion
2025-06-13 fix small mistake
2025-06-13 index error fix
2025-06-17 Fixed and updated README.md
2025-06-25 updated data and styles for a picture in report
2025-06-29 Try to fix responsibilities
2025-06-29 extra plebs
2025-07-07 dashboard update
2025-07-07 Updates to radio_module.py for testing
2025-07-13 fixed structure and text
2025-07-13 radio_module.py, added comments
2025-07-13 Updated text in index and renderer
2025-07-13 Comments on rfm69_utils
2025-07-13 update text in handler and data
2025-07-15 graphics changes
2025-07-15 Encoding.py
2025-07-15 Update: graphics, radio_module and rfm69_utils
2025-07-15 update text
2025-07-15 More comments to csv_handler
2025-07-16 Error fixing with kicad_dru, and silkscreeen updates. TO-DO: BOM to basic
2025-08-01 board update
2025-08-01 3D_files_rat
2025-08-01 PCB_Remake
2025-08-01 Rename folders for consistency
2025-08-01 updated .gitignore
2025-08-26 Rename Aflevering (1).pdf to light_system_introductory_project_report_2022
